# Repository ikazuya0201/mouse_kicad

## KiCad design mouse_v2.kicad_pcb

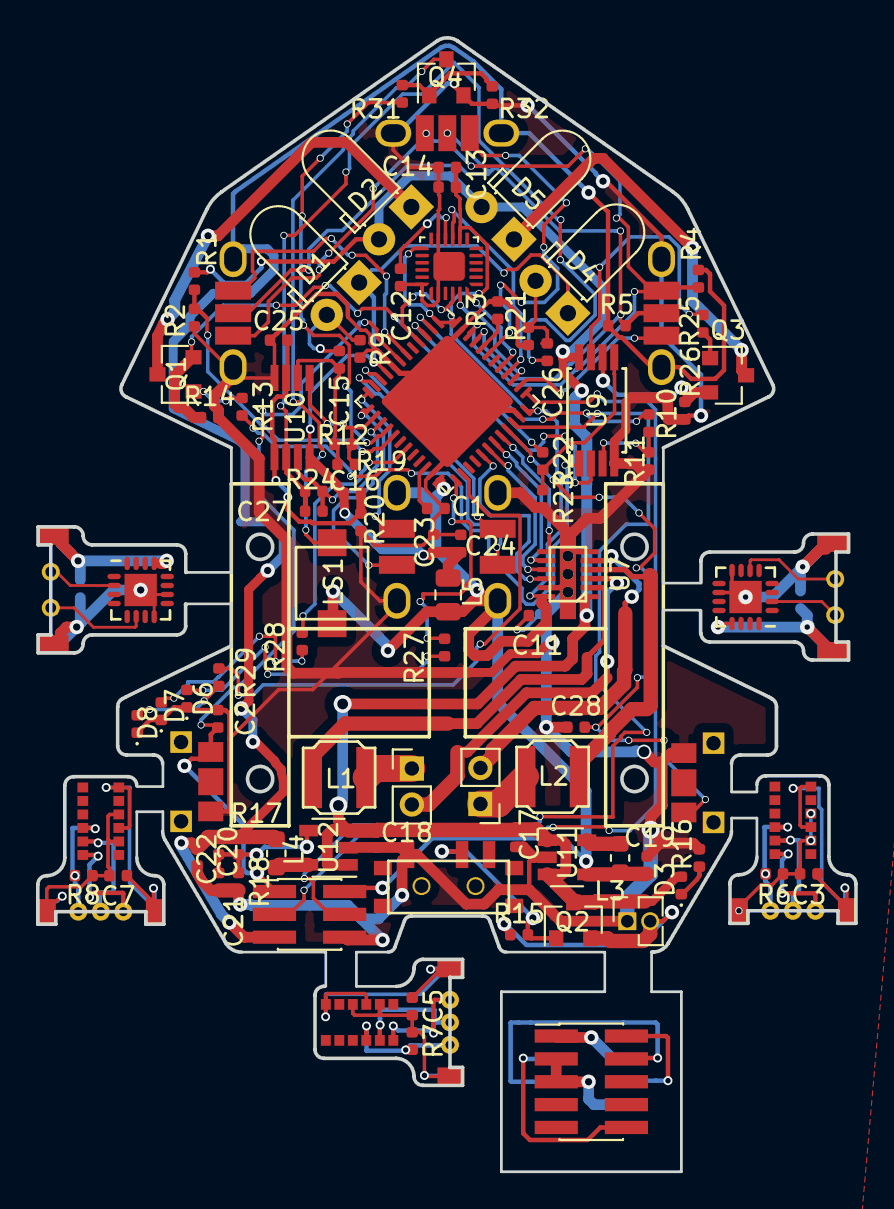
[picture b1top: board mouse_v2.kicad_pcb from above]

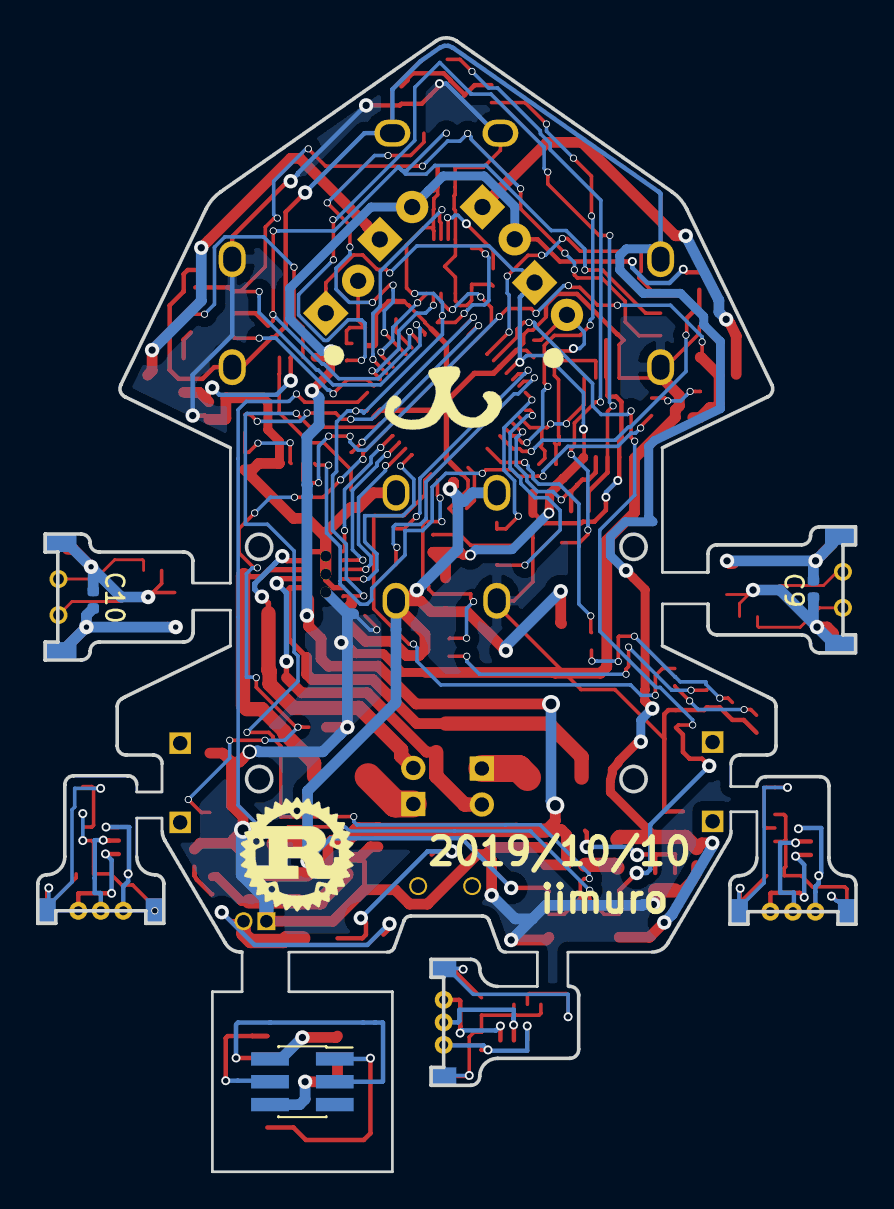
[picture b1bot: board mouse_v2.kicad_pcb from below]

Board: 2 copper layers, 45.5 x 63.0 mm, 79 parts (2 on the bottom side), 39 nets.

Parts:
C1: 2.2u; C_0402_1005Metric
C2, C11, C12, C13, C24, C25, C28: 0.1u; C_0402_1005Metric
C3, C5, C7, C17, C18: 4.7u; C_0402_1005Metric
C9, C10: 1u; C_0402_1005Metric
C14, C15, C26: 0.01u; C_0402_1005Metric
C16, C27: 22p; C_0402_1005Metric
C19, C22, C23: 10u; C_0402_1005Metric
C20: 24p; C_0402_1005Metric
C21: 110p; C_0402_1005Metric
D1, D4: SFH229FA; LED_D3.0mm_Horizontal_O1.27mm_Z2.0mm
D2, D5: OSCI5FU3A11C; LED_D3.0mm_Horizontal_O1.27mm_Z2.0mm
D3: BAT_LED; LED_0402_1005Metric
D6: LED1; LED_0402_1005Metric
D7: LED2; LED_0402_1005Metric
D8: LED3; LED_0402_1005Metric
L1, L2: 82u; ASPI-4030S
L3, L4: 10u; L_0603_1608Metric
L5: 100u; L_0805_2012Metric
LS1: SMT-0440-S-R
Q1, Q3, Q4: IRFML8244; SOT-23
Q2: IRLML6402; SOT-23
R1, R2, R3, R4, R5, R9, R10, R19, R20, R21, R22, R32: 10k; R_0402_1005Metric
R6, R7, R8: 47k; R_0402_1005Metric
R11, R23: 12k; R_0402_1005Metric
R12, R24: 2M; R_0402_1005Metric
R13, R25, R31: 10; R_0402_1005Metric
R14, R26: 10 1/5W; R_0402_1005Metric
R15: 100k; R_0402_1005Metric
R16, R27, R28, R29: 1k; R_0402_1005Metric
R17: 680k; R_0402_1005Metric
R18: 150k; R_0402_1005Metric
U7: DRV8835
U9: NJM2732; TSSOP-8_4.4x3mm_P0.65mm
U10: AD8602D; VSSOP-8_3.0x3.0mm_P0.65mm
U11: TPS62203DBV; SOT-23-5
U12: TPS62200DBV; SOT-23-5

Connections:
1.65V_REF: C25.1, R19.2, R20.1, U10.3, U10.5
2.8V: C20.1, C22.1, L4.1, R4.1, R5.1, R17.1
3.3V: C11.1, C13.1, C14.1, C19.1, L3.1, L5.2, LS1.1, U7.12, U11.4
3.3VA: C23.1, C24.1, D1.1, D4.1, L5.1, R19.1, U10.8
/MCU/BATT_MONITOR: R1.2, R2.1
/MCU/IR_ADC1: C16.1, R12.1, U10.1
/MCU/IR_ADC2: C27.1, R24.1, U10.7
/ToF1/2V8: C3.2, R6.1
/ToF2/2V8: C5.2, R7.1
/ToF3/2V8: C7.2, R8.1
BATT: C17.1, C18.1, D2.2, D3.2, D5.2, Q2.3, R1.1, U7.1, U9.8, U11.1, U11.3, U12.1, U12.3
GND: C1.2, C2.2, C11.2, C12.2, C13.2, C14.2, C17.2, C18.2, C19.2, C21.2, C22.2, C23.2, C24.2, C25.2, C28.1, D6.1, D7.1, D8.1, Q4.2, R2.2, R3.2, R9.2, R11.2, R14.2, R16.2, R18.2, R20.2, R21.2, R23.2, R26.2, R32.1, U7.6, U7.11, U7.13, U9.4, U10.4, U11.2, U12.2
unnamed: C15.1, C16.2, R12.2, U10.2
unnamed: C15.2, D1.2, R9.1
unnamed: C20.2, C21.1, R17.2, R18.1, U12.4
unnamed: C26.1, C27.2, R24.2, U10.6
unnamed: C26.2, D4.2, R21.1
unnamed: D2.1, Q1.3
unnamed: D3.1, R16.1
unnamed: D5.1, Q3.3
unnamed: D6.2, R27.1
unnamed: D7.2, R28.1
unnamed: D8.2, R29.1
unnamed: Q2.2, R15.1
unnamed: L1.2, U7.2
unnamed: L2.2, U7.4
unnamed: L3.2, U11.5
unnamed: L4.2, U12.5
unnamed: LS1.2, Q4.3
unnamed: Q1.1, R13.1
unnamed: Q1.2, R14.1, U9.2
unnamed: Q2.1, R15.2
unnamed: Q3.1, R25.1
unnamed: Q3.2, R26.1, U9.6
unnamed: Q4.1, R31.1, R32.2
unnamed: R10.2, R11.1, U9.3
unnamed: R13.2, U9.1
unnamed: R22.2, R23.1, U9.5
unnamed: R25.2, U9.7

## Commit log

2019-04-15 [add] Initial commit.
2019-04-28 [add] Circuit design almost finished.
2019-05-06 [add] Completed parts placement.
2019-05-07 [add] Finished to manual routing.
2019-05-09 [add] Completed routing.
2019-05-09 [add] Finished to organize silks.
2020-02-10 [update] Modified height of encoder board.
2020-02-10 [delete] Removed .DS_Store.
2020-02-10 [update] Renamed mouse_v2 to mouse.
2020-02-10 [delete] Removed files for elecrow.
